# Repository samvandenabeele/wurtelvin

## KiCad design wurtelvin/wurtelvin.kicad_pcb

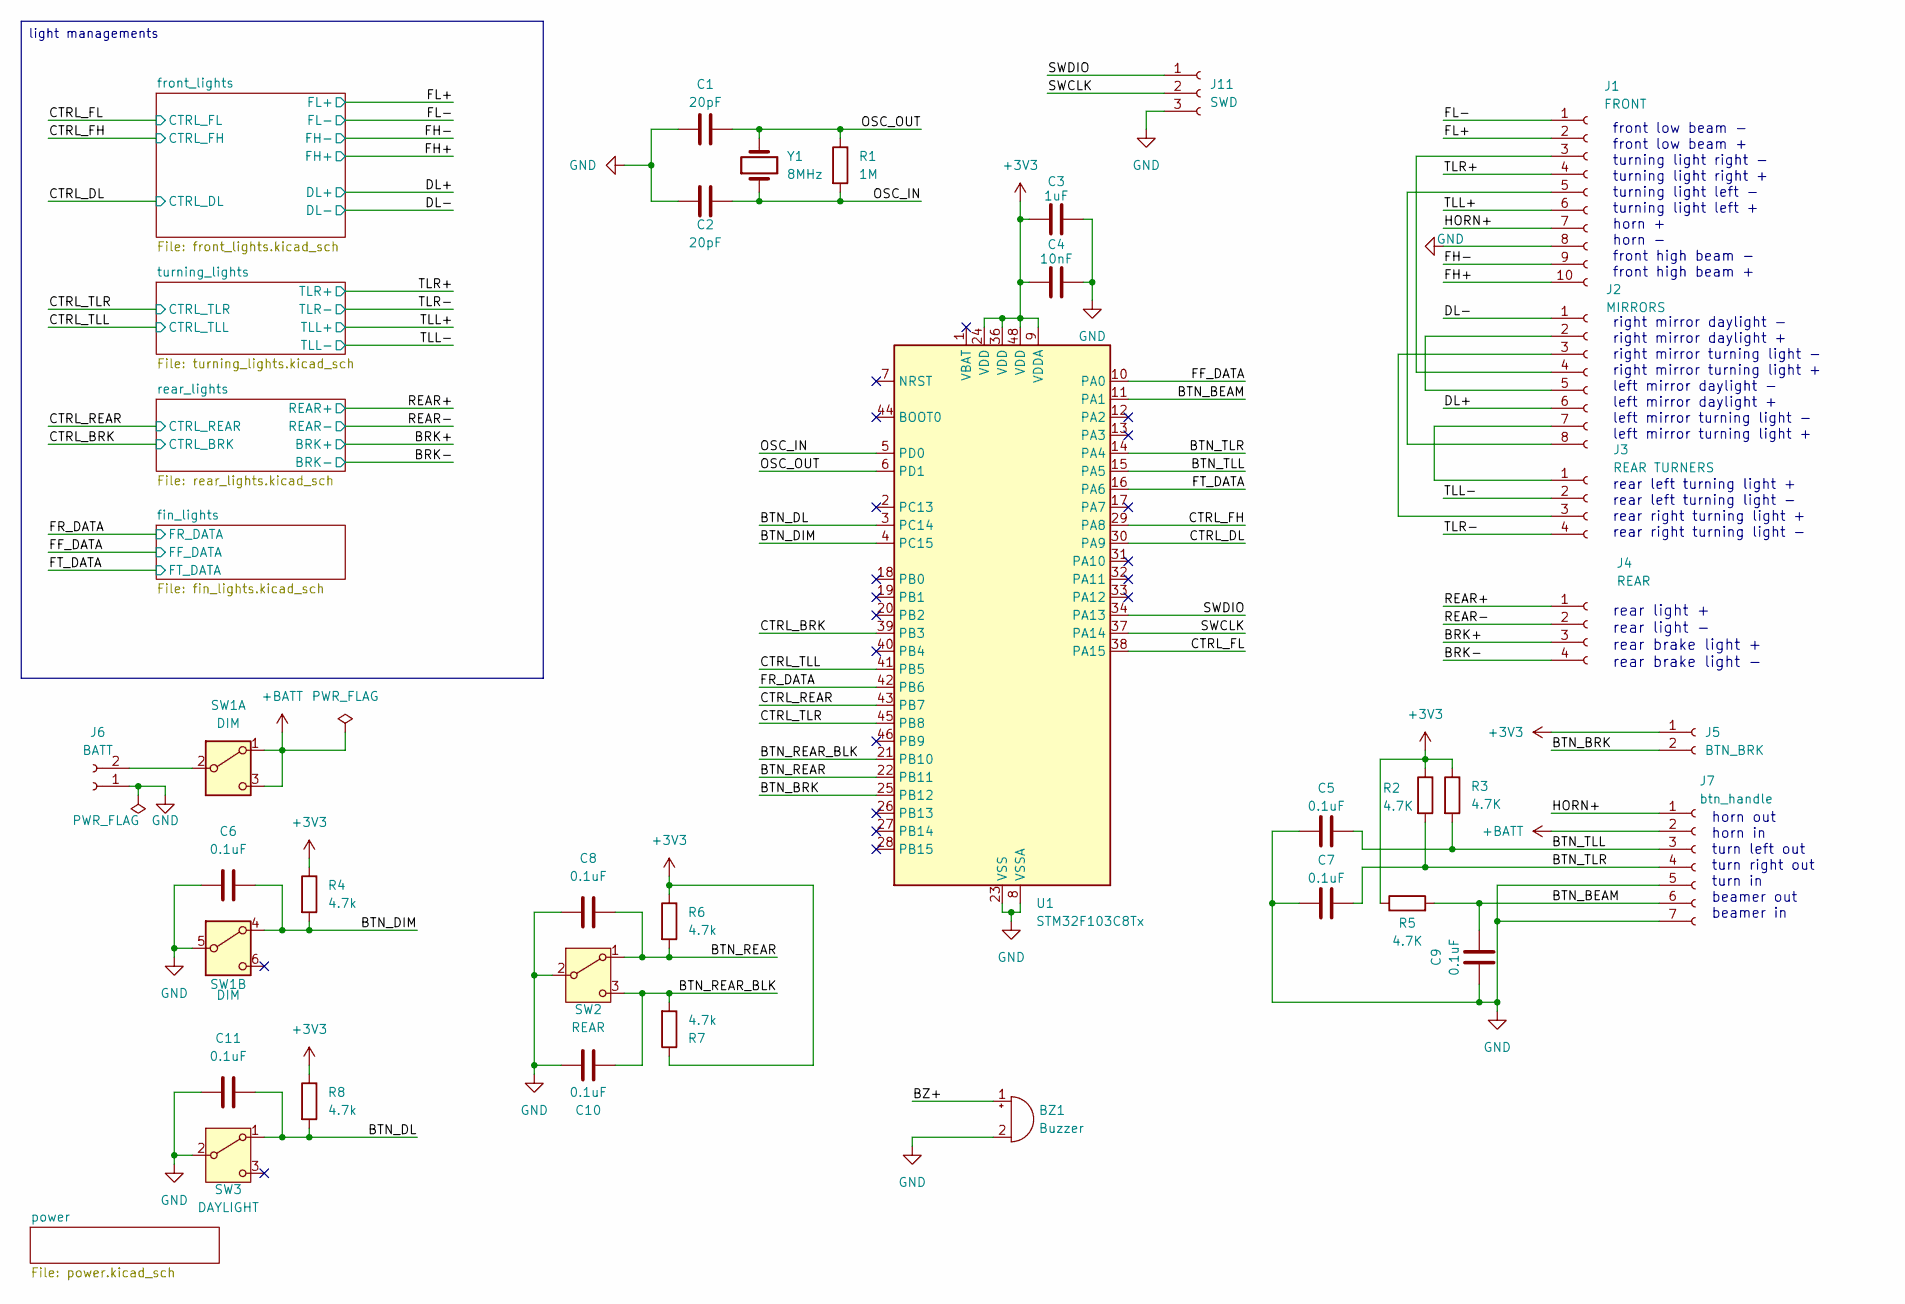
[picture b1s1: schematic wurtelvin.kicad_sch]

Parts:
BZ1: Buzzer; Indicator_PUI_AI-1440-TWT-24V-2-R; MPN AI-1440-TWT-12V-R
C1, C2: 20pF; C_0603_1608Metric; MPN CL10C200JB8NNNC
C3: 1uF; C_0603_1608Metric; MPN C0603C105K4RACTU
C4: 10nF; C_0603_1608Metric; MPN C0603C103K5RACTU
C5, C6, C7, C8, C9, C10, C11: 0.1uF; C_0603_1608Metric; MPN C0603C104K5RACTU
J1: FRONT; JST_PHD_S10B-PHDSS_2x05_P2.00mm_Horizontal; MPN S10B-PHDSS
J2: MIRRORS; JST_PH_S8B-PH-SM4-TB_1x08-1MP_P2.00mm_Horizontal; MPN S8B-PH-SM4-TB
J3: REAR TURNERS; JST_PH_S4B-PH-SM4-TB_1x04-1MP_P2.00mm_Horizontal; MPN S4B-PH-SM4-TB
J4: REAR; JST_PH_S4B-PH-SM4-TB_1x04-1MP_P2.00mm_Horizontal; MPN S4B-PH-SM4-TB
J5: BTN_BRK; JST_PH_S2B-PH-SM4-TB_1x02-1MP_P2.00mm_Horizontal; MPN S2B-PH-SM4-TB
J6: BATT; JST_PH_S2B-PH-SM4-TB_1x02-1MP_P2.00mm_Horizontal; MPN S2B-PH-SM4-TB
J7: btn_handle; JST_PH_S7B-PH-SM4-TB_1x07-1MP_P2.00mm_Horizontal; MPN S7B-PH-SM4-TB
J11: SWD; PinHeader_1x03_P1.27mm_Vertical
R1: 1M; R_0603_1608Metric
R2, R3, R5: 4.7K; R_0603_1608Metric
R4, R6, R7, R8: 4.7k; R_0603_1608Metric
SW1: DIM; ANT_2x3; MPN ANT23SECQE
SW2: REAR; ANT_1x3; MPN ANT13SECQE
SW3: DAYLIGHT; ANT_1x3; MPN ANT13SECQE
U1: STM32F103C8Tx; LQFP-48_7x7mm_P0.5mm; MPN STM32F103C8T6
Y1: 8MHz; Crystal_SMD_Abracon_ABM3-2Pin_5.0x3.2mm; MPN ABM3-8.000MHZ-D2Y-T

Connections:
+3V3: C3.1, C4.1, J5.1, R2.1, R3.1, R4.1, R5.1, R6.1, R7.1, R8.1, U1.9 (VDDA), U1.24 (VDD), U1.36 (VDD), U1.48 (VDD); also elsewhere on the board
+BATT: J7.2, SW1.1 (A), SW1.3 (C); also elsewhere on the board
/BRK+: J4.3; also elsewhere on the board
/BRK-: J4.4; also elsewhere on the board
/BTN_BEAM: C9.2, J7.6, R5.2, U1.11 (PA1)
/BTN_BRK: J5.2, U1.25 (PB12)
/BTN_DIM: C6.2, R4.2, SW1.4 (A), U1.4 (PC15)
/BTN_DL: C11.2, R8.2, SW3.1 (A), U1.3 (PC14)
/BTN_REAR: C8.2, R6.2, SW2.1 (A), U1.22 (PB11)
/BTN_REAR_BLK: C10.2, R7.2, SW2.3 (C), U1.21 (PB10)
/BTN_TLL: C5.2, J7.3, R3.2, U1.15 (PA5)
/BTN_TLR: C7.2, J7.4, R2.2, U1.14 (PA4)
/BZ+: BZ1.1 (+)
/CTRL_BRK: U1.39 (PB3); also elsewhere on the board
/CTRL_DL: U1.30 (PA9); also elsewhere on the board
/CTRL_FH: U1.29 (PA8); also elsewhere on the board
/CTRL_FL: U1.38 (PA15); also elsewhere on the board
/CTRL_REAR: U1.43 (PB7); also elsewhere on the board
/CTRL_TLL: U1.41 (PB5); also elsewhere on the board
/CTRL_TLR: U1.45 (PB8); also elsewhere on the board
/DL+: J2.6; also elsewhere on the board
/DL-: J2.1; also elsewhere on the board
/FF_DATA: U1.10 (PA0); also elsewhere on the board
/FH+: J1.10; also elsewhere on the board
/FH-: J1.9; also elsewhere on the board
/FL+: J1.2; also elsewhere on the board
/FL-: J1.1; also elsewhere on the board
/FR_DATA: U1.42 (PB6); also elsewhere on the board
/FT_DATA: U1.16 (PA6); also elsewhere on the board
/HORN+: J1.7, J7.1
/OSC_IN: C2.2, R1.2, U1.5 (PD0), Y1.1
/OSC_OUT: C1.2, R1.1, U1.6 (PD1), Y1.2
/REAR+: J4.1; also elsewhere on the board
/REAR-: J4.2; also elsewhere on the board
/SWCLK: J11.2, U1.37 (PA14)
/SWDIO: J11.1, U1.34 (PA13)
/TLL+: J1.6; also elsewhere on the board
/TLL-: J3.2; also elsewhere on the board
/TLR+: J1.4; also elsewhere on the board
/TLR-: J3.4; also elsewhere on the board
GND: BZ1.2 (-), C1.1, C2.1, C3.2, C4.2, C5.1, C6.1, C7.1, C8.1, C9.1, C10.1, C11.1, J1.8, J6.1, J7.5, J7.7, J11.3, SW1.5 (B), SW2.2 (B), SW3.2 (B), U1.8 (VSSA), U1.23 (VSS), U1.35 (VSS), U1.47 (VSS); also elsewhere on the board
unnamed: J1.3, J2.4
unnamed: J1.5, J2.8
unnamed: J2.2, J2.5
unnamed: J2.3, J3.3
unnamed: J2.7, J3.1
unnamed: J6.2, SW1.2 (B)

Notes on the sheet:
front low beam - front low beam + turning light right - turning light right + turning light left - turning light left + horn + horn - front high beam - front high beam +
right mirror daylight - right mirror daylight + right mirror turning light - right mirror turning light + left mirror daylight - left mirror daylight + left mirror turning light - left mirror turning light +
rear left turning light + rear left turning light - rear right turning light + rear right turning light -
rear light + rear light - rear brake light + rear brake light -
horn out horn in turn left out turn right out turn in beamer out beamer in
light managements

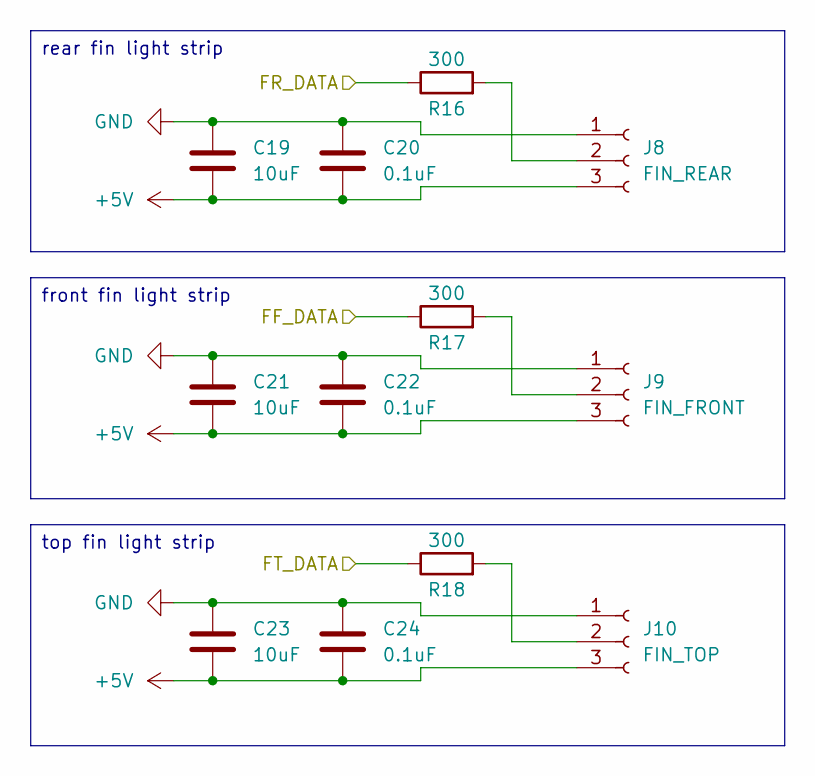
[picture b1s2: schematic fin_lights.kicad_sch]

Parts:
C19, C21, C23: 10uF; C_0603_1608Metric; MPN GRM188R60J106ME47D
C20, C22, C24: 0.1uF; C_0603_1608Metric; MPN C0603C104K5RACTU
J8: FIN_REAR; JST_PH_S3B-PH-SM4-TB_1x03-1MP_P2.00mm_Horizontal; MPN S3B-PH-SM4-TB
J9: FIN_FRONT; JST_PH_S3B-PH-SM4-TB_1x03-1MP_P2.00mm_Horizontal; MPN S3B-PH-SM4-TB
J10: FIN_TOP; JST_PH_S3B-PH-SM4-TB_1x03-1MP_P2.00mm_Horizontal; MPN S3B-PH-SM4-TB
R16, R17, R18: 300; R_0603_1608Metric

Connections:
+5V: C19.2, C20.2, C21.2, C22.2, C23.2, C24.2, J8.3, J9.3, J10.3; also elsewhere on the board
/FF_DATA: R17.1; also elsewhere on the board
/FR_DATA: R16.1; also elsewhere on the board
/FT_DATA: R18.1; also elsewhere on the board
GND: C19.1, C20.1, C21.1, C22.1, C23.1, C24.1, J8.1, J9.1, J10.1; also elsewhere on the board
unnamed: J8.2, R16.2
unnamed: J9.2, R17.2
unnamed: J10.2, R18.2

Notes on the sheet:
top fin light strip
front fin light strip
rear fin light strip

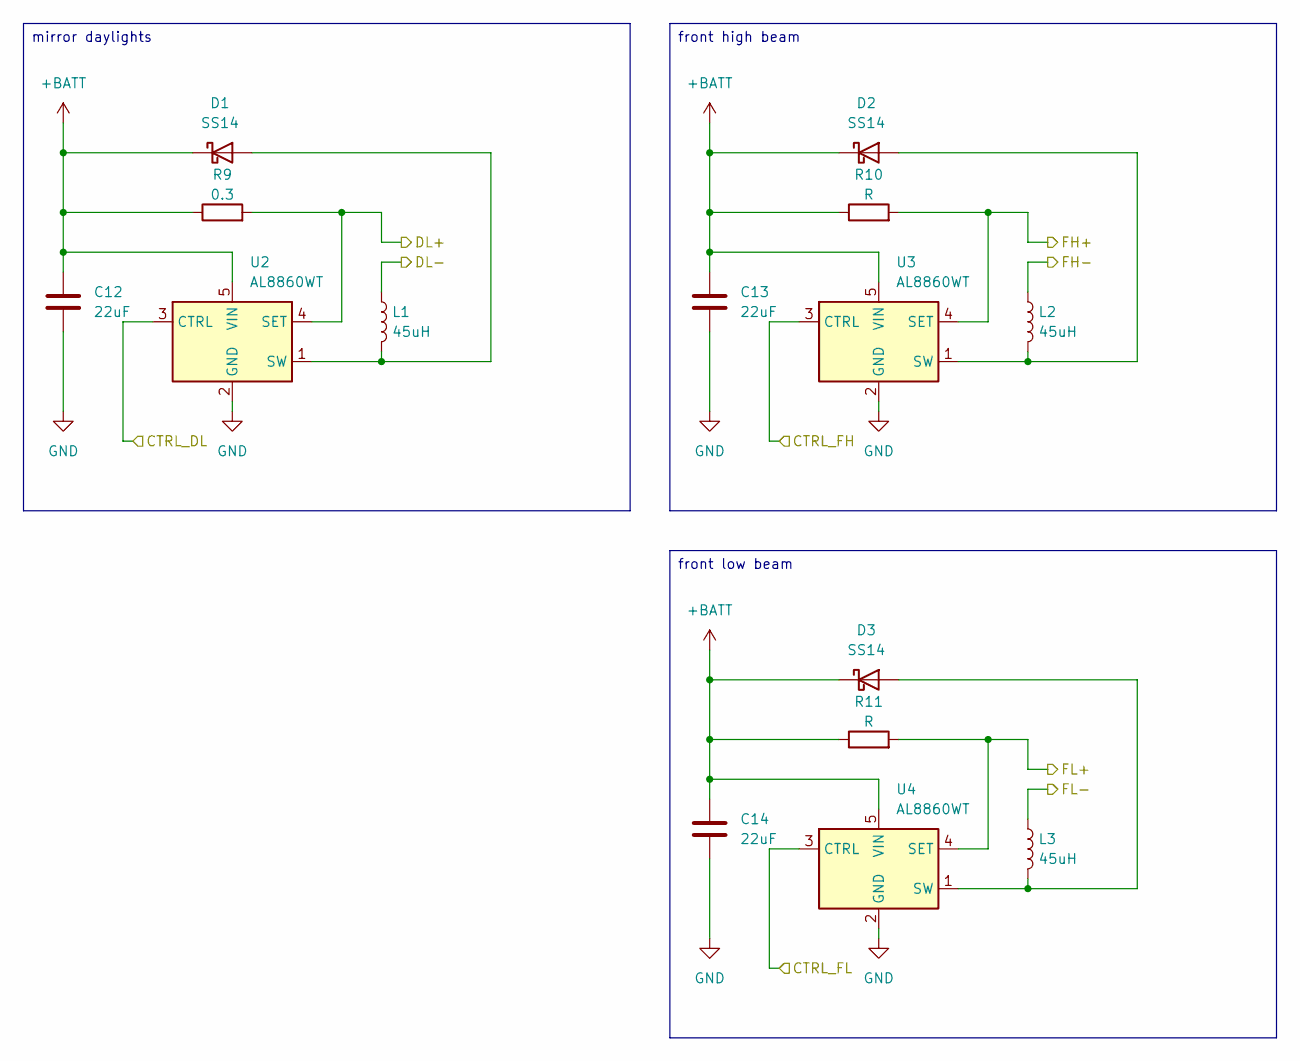
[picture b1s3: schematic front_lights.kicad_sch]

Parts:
C12, C13, C14: 22uF; C_0603_1608Metric; MPN CL10A226KQ8NRNE
D1, D2, D3: SS14; D_SMA; MPN SS14
L1, L2, L3: 45uH; L_TDK_VLS6045EX_VLS6045AF; MPN 810-VLS6045EX-470M
R9: 0.3; R_0603_1608Metric
R10, R11: R; R_0603_1608Metric
U2, U3, U4: AL8860WT; TSOT-23-5; MPN AL8860WT-7

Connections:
+BATT: C12.1, C13.1, C14.1, D1.1 (K), D2.1 (K), D3.1 (K), R9.1, R10.1, R11.1, U2.5 (VIN), U3.5 (VIN), U4.5 (VIN); also elsewhere on the board
/CTRL_DL: U2.3 (CTRL); also elsewhere on the board
/CTRL_FH: U3.3 (CTRL); also elsewhere on the board
/CTRL_FL: U4.3 (CTRL); also elsewhere on the board
/DL+: R9.2, U2.4 (SET); also elsewhere on the board
/DL-: L1.1; also elsewhere on the board
/FH+: R10.2, U3.4 (SET); also elsewhere on the board
/FH-: L2.1; also elsewhere on the board
/FL+: R11.2, U4.4 (SET); also elsewhere on the board
/FL-: L3.1; also elsewhere on the board
GND: C12.2, C13.2, C14.2, U2.2 (GND), U3.2 (GND), U4.2 (GND); also elsewhere on the board
unnamed: D1.2 (A), L1.2, U2.1 (SW)
unnamed: D2.2 (A), L2.2, U3.1 (SW)
unnamed: D3.2 (A), L3.2, U4.1 (SW)

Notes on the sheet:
front high beam
front low beam
mirror daylights

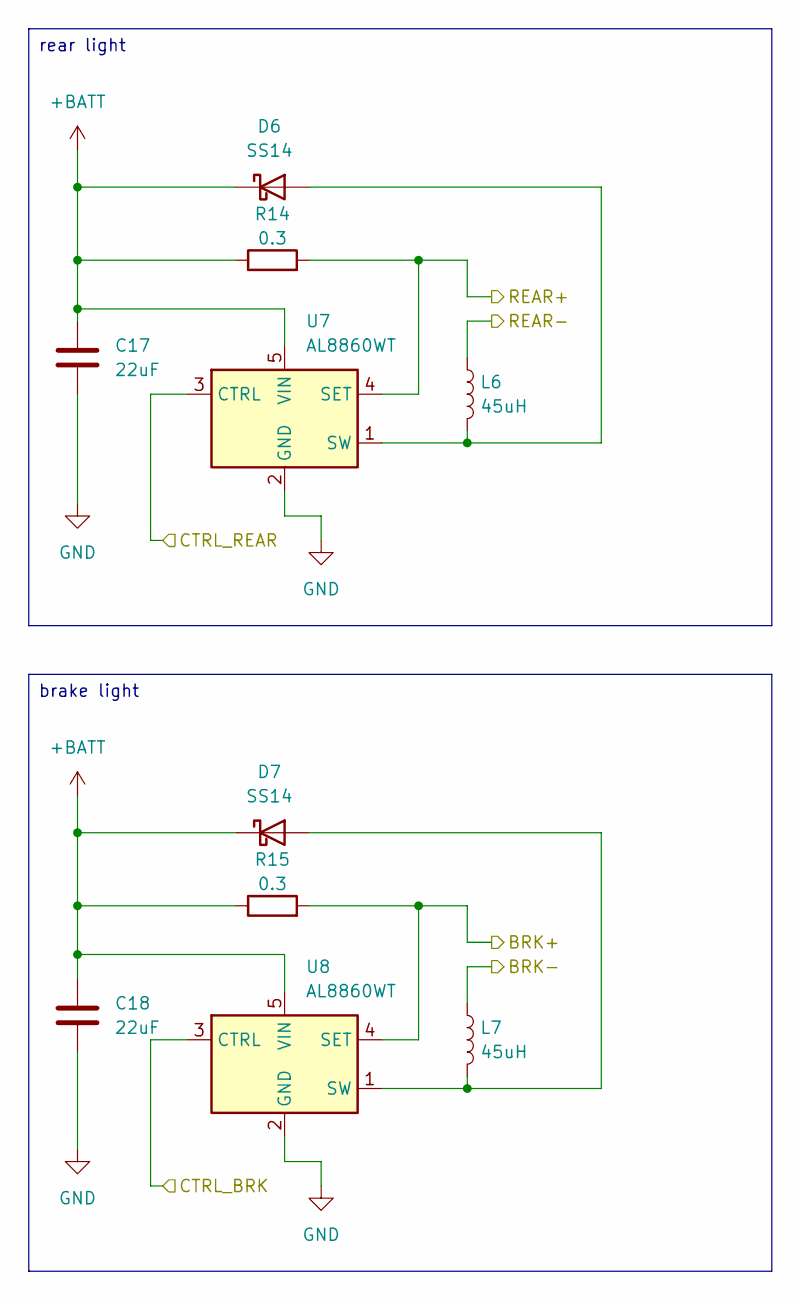
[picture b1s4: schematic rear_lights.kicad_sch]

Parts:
C17, C18: 22uF; C_0603_1608Metric; MPN CL10A226KQ8NRNE
D6, D7: SS14; D_SMA; MPN SS14
L6, L7: 45uH; L_TDK_VLS6045EX_VLS6045AF; MPN 810-VLS6045EX-470M
R14, R15: 0.3; R_0603_1608Metric
U7, U8: AL8860WT; TSOT-23-5; MPN AL8860WT-7

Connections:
+BATT: C17.1, C18.1, D6.1 (K), D7.1 (K), R14.1, R15.1, U7.5 (VIN), U8.5 (VIN); also elsewhere on the board
/BRK+: R15.2, U8.4 (SET); also elsewhere on the board
/BRK-: L7.1; also elsewhere on the board
/CTRL_BRK: U8.3 (CTRL); also elsewhere on the board
/CTRL_REAR: U7.3 (CTRL); also elsewhere on the board
/REAR+: R14.2, U7.4 (SET); also elsewhere on the board
/REAR-: L6.1; also elsewhere on the board
GND: C17.2, C18.2, U7.2 (GND), U8.2 (GND); also elsewhere on the board
unnamed: D6.2 (A), L6.2, U7.1 (SW)
unnamed: D7.2 (A), L7.2, U8.1 (SW)

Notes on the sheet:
rear light
brake light

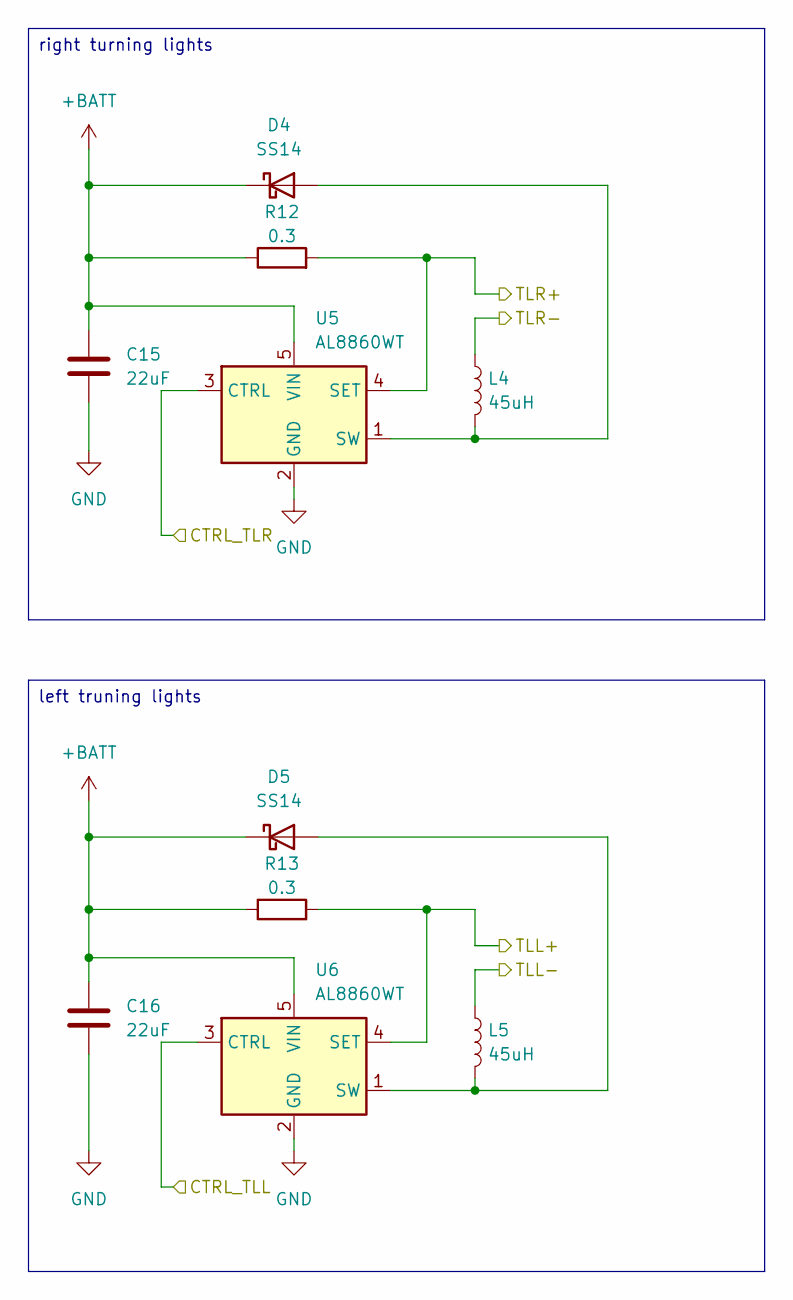
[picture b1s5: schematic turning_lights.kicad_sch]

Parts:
C15, C16: 22uF; C_0603_1608Metric; MPN CL10A226KQ8NRNE
D4, D5: SS14; D_SMA; MPN SS14
L4, L5: 45uH; L_TDK_VLS6045EX_VLS6045AF; MPN 810-VLS6045EX-470M
R12, R13: 0.3; R_0603_1608Metric
U5, U6: AL8860WT; TSOT-23-5; MPN AL8860WT-7

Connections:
+BATT: C15.1, C16.1, D4.1 (K), D5.1 (K), R12.1, R13.1, U5.5 (VIN), U6.5 (VIN); also elsewhere on the board
/CTRL_TLL: U6.3 (CTRL); also elsewhere on the board
/CTRL_TLR: U5.3 (CTRL); also elsewhere on the board
/TLL+: R13.2, U6.4 (SET); also elsewhere on the board
/TLL-: L5.1; also elsewhere on the board
/TLR+: R12.2, U5.4 (SET); also elsewhere on the board
/TLR-: L4.1; also elsewhere on the board
GND: C15.2, C16.2, U5.2 (GND), U6.2 (GND); also elsewhere on the board
unnamed: D4.2 (A), L4.2, U5.1 (SW)
unnamed: D5.2 (A), L5.2, U6.1 (SW)

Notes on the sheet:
right turning lights
left truning lights

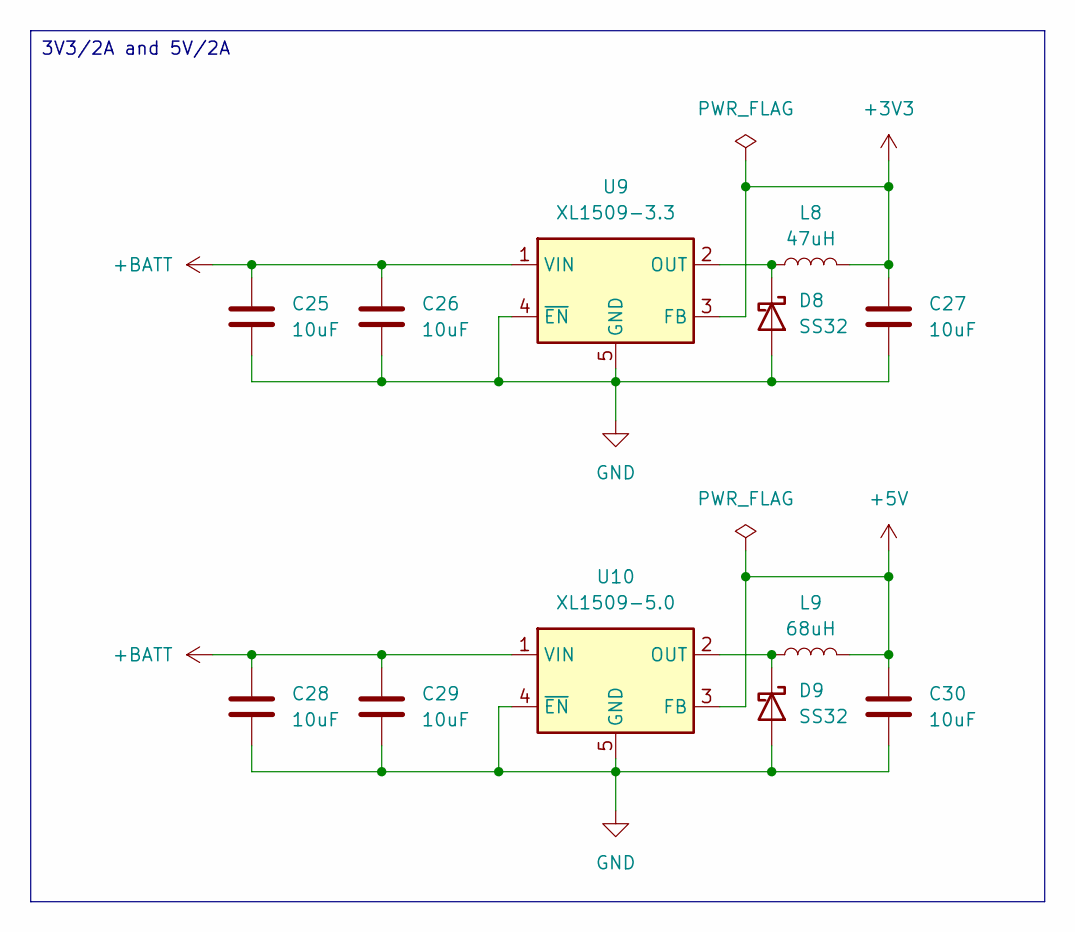
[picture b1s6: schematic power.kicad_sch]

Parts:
C25, C26, C27, C28, C29, C30: 10uF; C_0603_1608Metric; MPN GRM188R60J106ME47D
D8, D9: SS32; D_SMA; MPN SS32
L8: 47uH; L_TDK_VLS6045EX_VLS6045AF; MPN 810-VLS6045EX-470M
L9: 68uH; L_TDK_VLS6045EX_VLS6045AF; MPN 810-VLS6045EX-680M
U9: XL1509-3.3; SOIC-8_3.9x4.9mm_P1.27mm; MPN XL1509-3.3
U10: XL1509-5.0; SOIC-8_3.9x4.9mm_P1.27mm; MPN XL1509-5.0

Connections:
+3V3: C27.1, L8.2, U9.3 (FB); also elsewhere on the board
+5V: C30.1, L9.2, U10.3 (FB); also elsewhere on the board
+BATT: C25.1, C26.1, C28.1, C29.1, U9.1 (VIN), U10.1 (VIN); also elsewhere on the board
GND: C25.2, C26.2, C27.2, C28.2, C29.2, C30.2, D8.2 (A), D9.2 (A), U9.4 (~EN), U9.5 (GND), U9.6 (GND), U9.7 (GND), U9.8 (GND), U10.4 (~EN), U10.5 (GND), U10.6 (GND), U10.7 (GND), U10.8 (GND); also elsewhere on the board
unnamed: D8.1 (K), L8.1, U9.2 (OUT)
unnamed: D9.1 (K), L9.1, U10.2 (OUT)

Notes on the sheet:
3V3/2A and 5V/2A

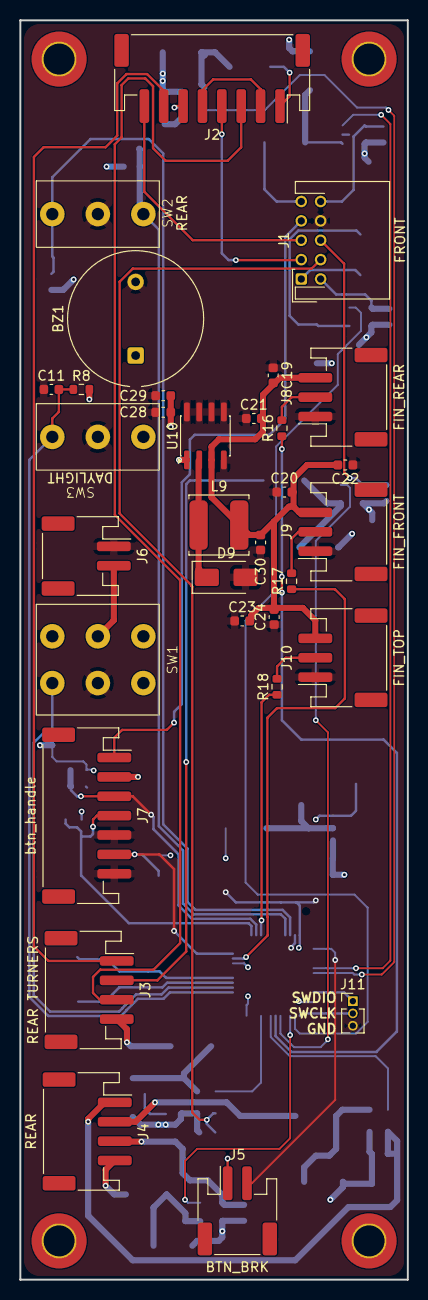
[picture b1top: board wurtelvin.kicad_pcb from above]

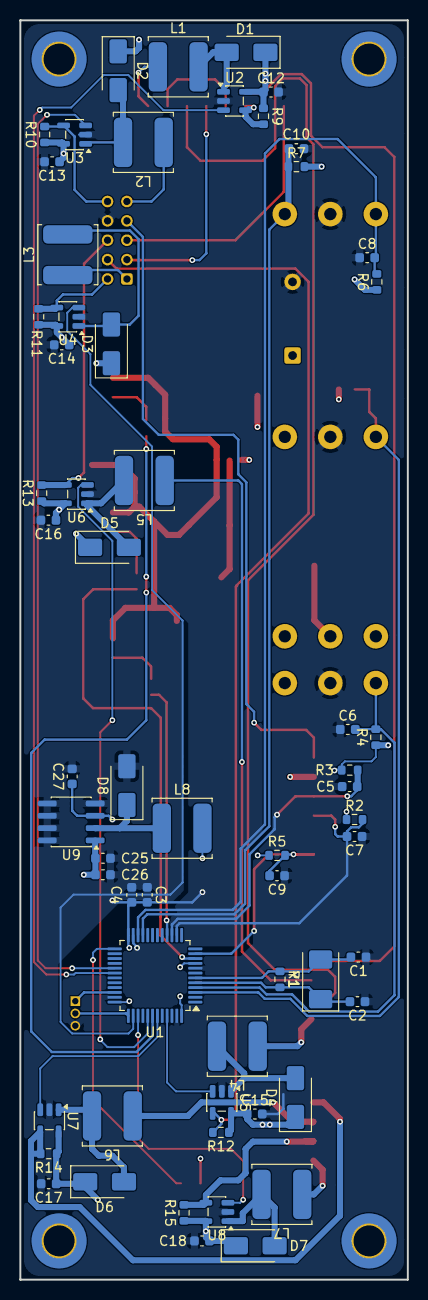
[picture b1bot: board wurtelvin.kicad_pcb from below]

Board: 4 copper layers, 40.0 x 130.0 mm, 92 parts (60 on the bottom side), 59 nets.
